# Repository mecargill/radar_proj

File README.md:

You can find a description of this radar project on https://mecargill.github.io/portfolio_page/.

Mcu_fmcw_manager is code for an STM32 f446. It buffers data from the ADC and sends it over SPI to the master (a raspberry pi in my case).
It also sends a triangle wave to the DAC.

Fmcw_pcb contains the KiCAD project in which I made the schematic and PCB for the radar.

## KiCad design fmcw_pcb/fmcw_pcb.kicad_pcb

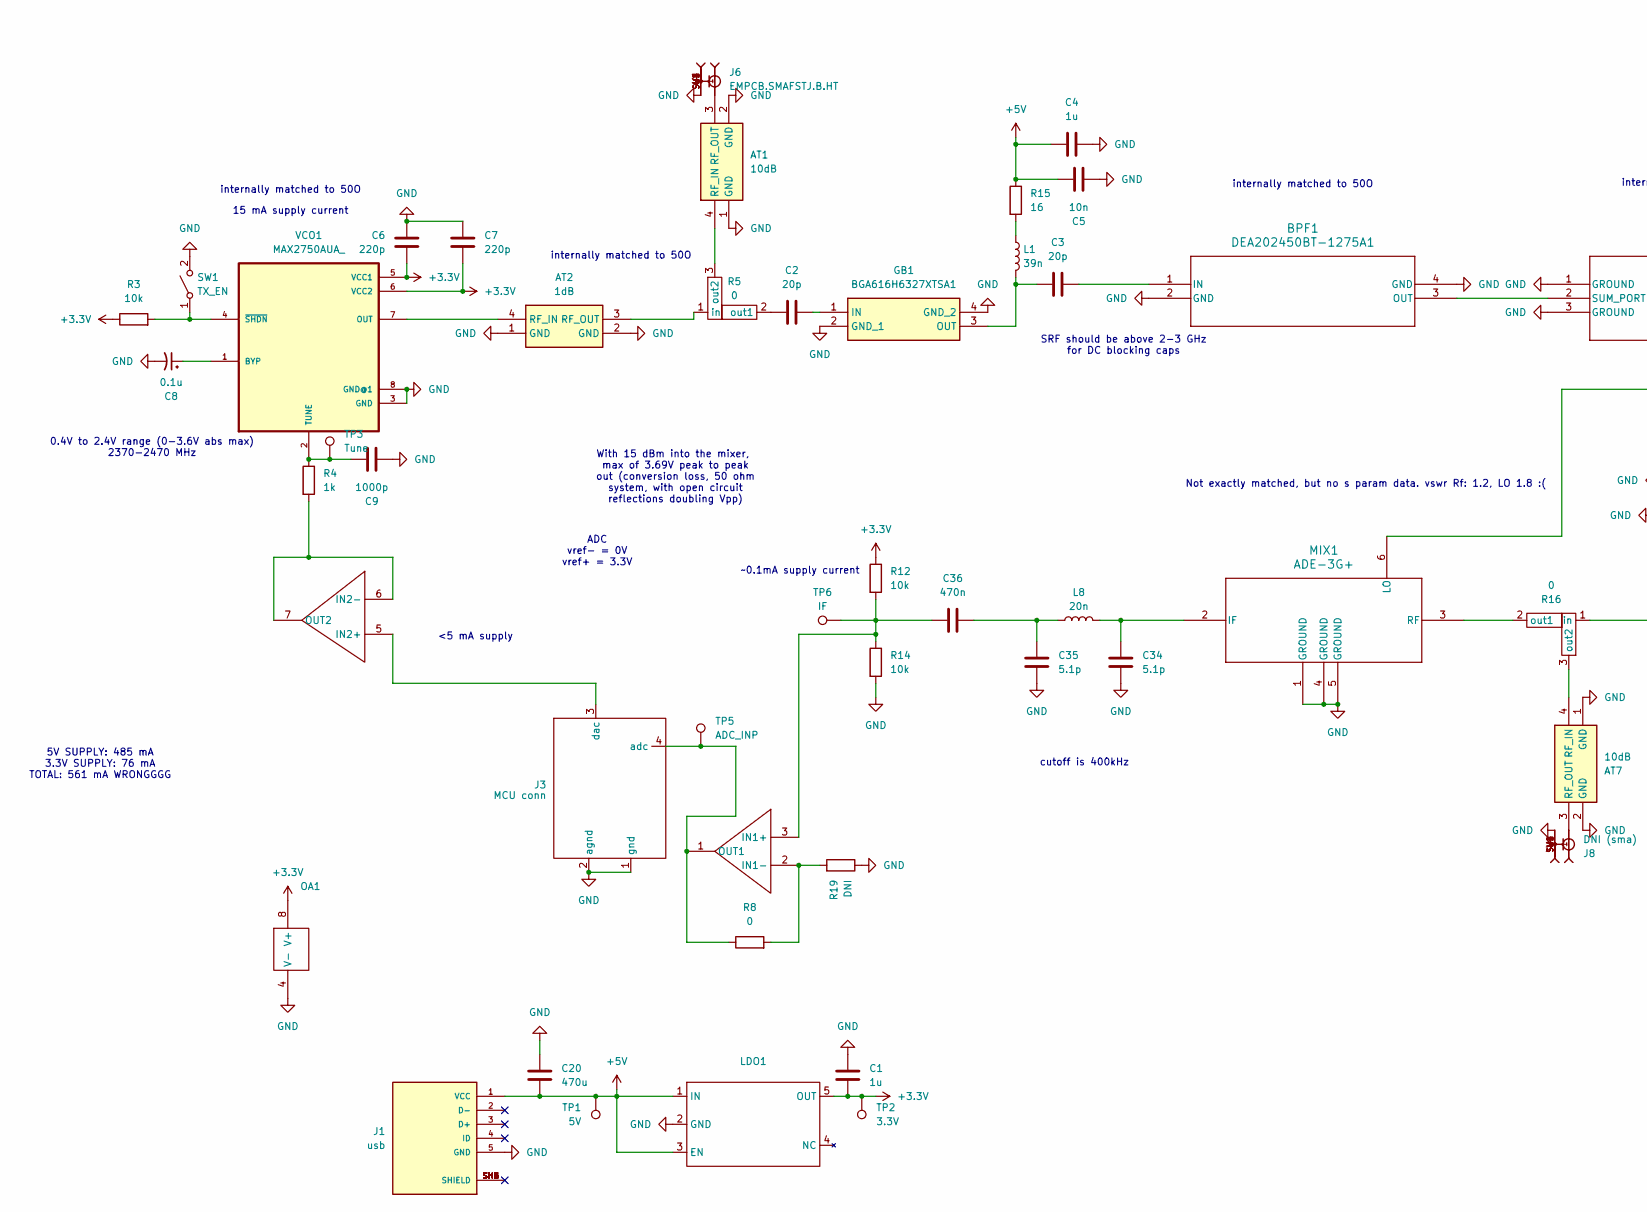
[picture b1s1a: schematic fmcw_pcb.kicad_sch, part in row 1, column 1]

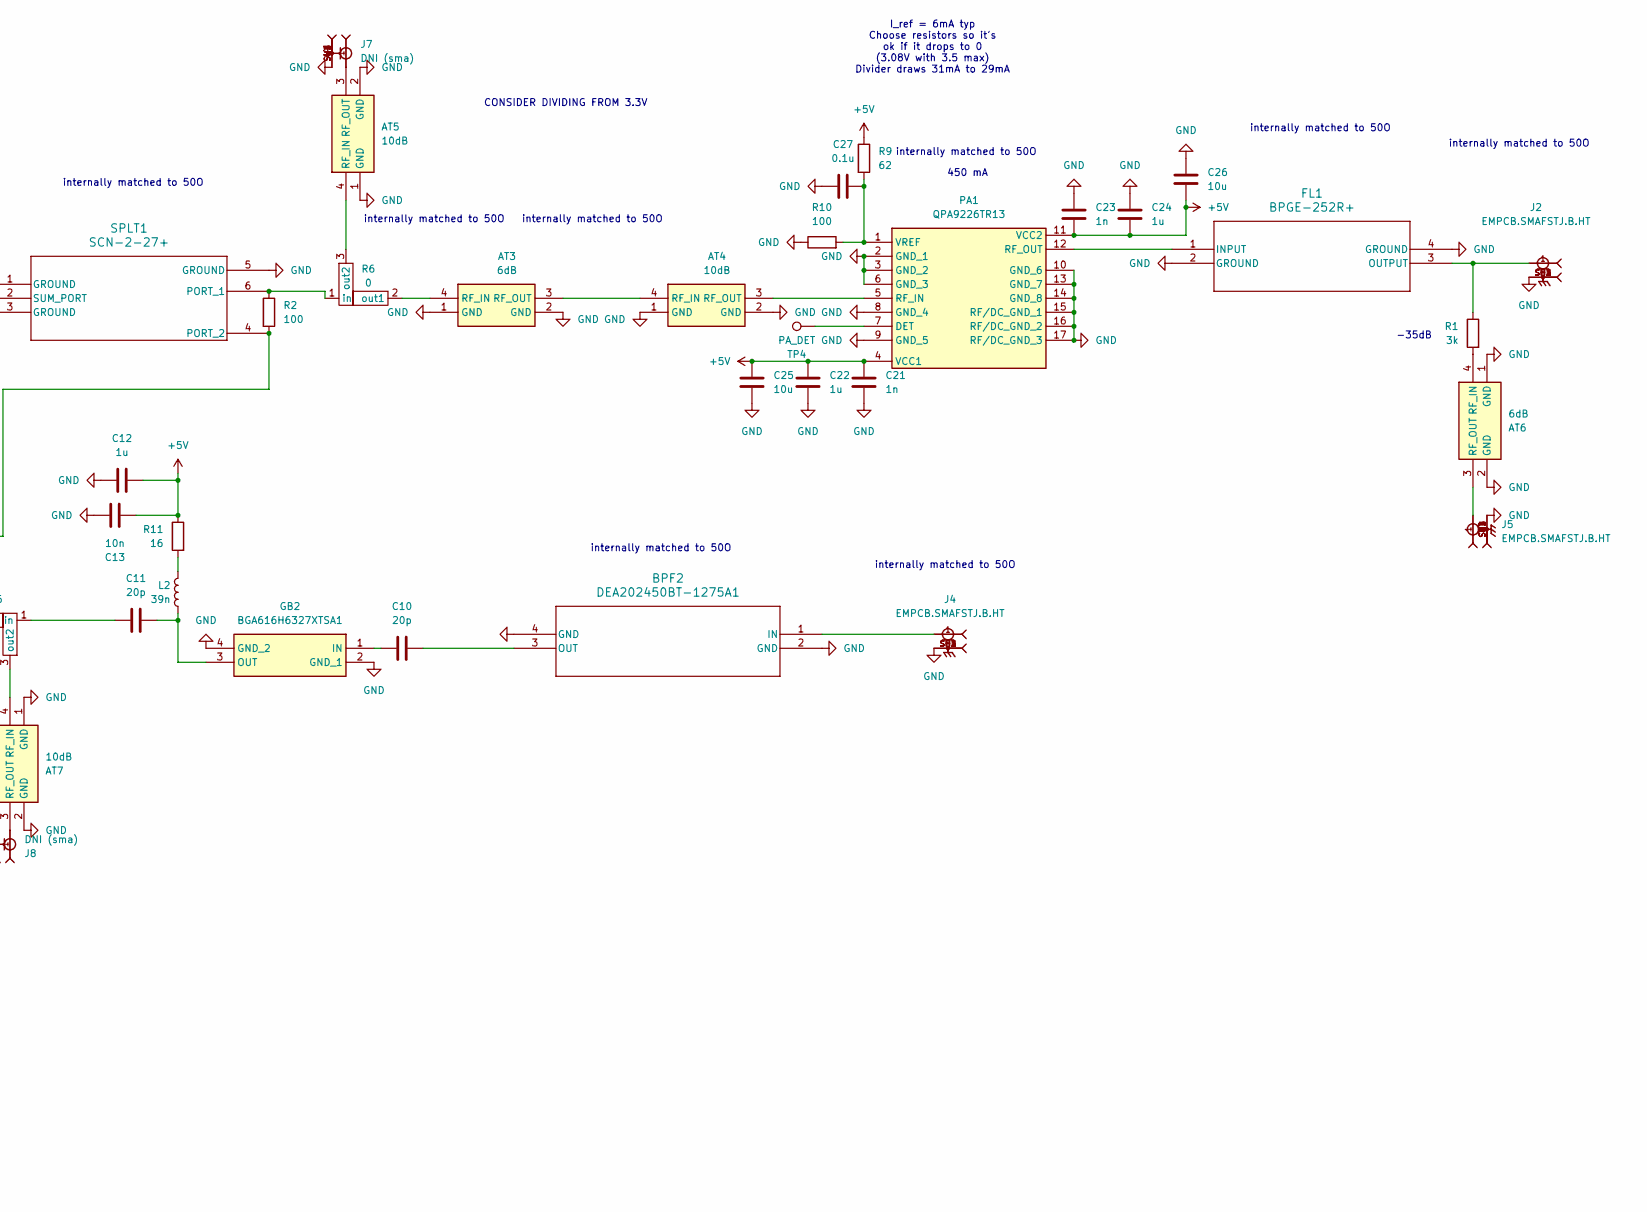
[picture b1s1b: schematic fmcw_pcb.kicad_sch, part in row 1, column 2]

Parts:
AT1, AT4, AT5, AT7: 10dB; EXB24AT6AR5X; Manufacturer_Part_Number EXB-24AT6AR5X; Mouser Part Number 667-EXB-24AT6AR5X
AT2: 1dB; EXB24AT6AR5X; Manufacturer_Part_Number EXB-24AT6AR5X; Mouser Part Number 667-EXB-24AT6AR5X
AT3, AT6: 6dB; EXB24AT6AR5X; Manufacturer_Part_Number EXB-24AT6AR5X; Mouser Part Number 667-EXB-24AT6AR5X
BPF1, BPF2: DEA202450BT-1275A1; DEA-4_2P0X1P25
C1, C4, C12, C22, C24: 1u; C_0805_2012Metric
C2, C3, C10, C11: 20p; C_0603_1608Metric
C5, C13: 10n; C_0805_2012Metric
C6, C7: 220p; C_0603_1608Metric
C8, C27: 0.1u; C_0805_2012Metric
C9: 1000p; C_0805_2012Metric
C20: 470u; CP_Radial_D7.5mm_P2.50mm
C21, C23: 1n; C_0805_2012Metric
C25, C26: 10u; CP_EIA-6032-15_Kemet-U
C34, C35: 5.1p; C_0603_1608Metric
C36: 470n; C_0805_2012Metric
FL1: BPGE-252R+; GE0805C-3_MNC
GB1, GB2: BGA616H6327XTSA1; Manufacturer_Part_Number BGA616H6327XTSA1; Mouser Part Number 726-BGA616H6327XTSA1
J1: usb; AMPHENOL_10118194-0001LF; PARTREV D
J2, J4, J5, J6: EMPCB.SMAFSTJ.B.HT; sma_1.6mm; DigiKey_Part_Number 931-1175-ND
J3: MCU conn; FanPinHeader_1x04_P2.54mm_Vertical
J7, J8: DNI (sma); sma_1.6mm; DigiKey_Part_Number 931-1175-ND
L1, L2: 39n; L_0603_1608Metric
L8: 20n; L_0603_1608Metric
LDO1: SOT95P280X145-5N(ldo)
MIX1: ADE-3G+; Mini-Circuits_CD542_LandPatternPL-052
OA1: SOT65P280X110-8N(op_amp)
PA1: QPA9226TR13; Mouser Part Number 772-QPA9226TR13
R1: 3k; R_0805_2012Metric
R2, R10: 100; R_0805_2012Metric
R3, R12, R14: 10k; R_0805_2012Metric
R4: 1k; R_0805_2012Metric
R5, R6, R16: 0; 2way_jumper
R8: 0; R_0805_2012Metric
R9: 62; R_0805_2012Metric
R11, R15: 16; R_0805_2012Metric
R19: DNI; R_0805_2012Metric
SPLT1: SCN-2-27+; Filter_Mini-Circuits_FV1206-1
SW1: TX_EN; PinHeader_1x02_P2.54mm_Vertical
TP1: 5V; TestPoint_Pad_2.5x2.5mm
TP2: 3.3V; TestPoint_Pad_2.5x2.5mm
TP3: Tune; TestPoint_Pad_2.5x2.5mm
TP4: PA_DET; TestPoint_Pad_2.5x2.5mm
TP5: ADC_INP; TestPoint_Pad_2.5x2.5mm
TP6: IF; TestPoint_Pad_2.5x2.5mm
VCO1: MAX2750AUA_; SOP65P490X110-8N; DigiKey_Part_Number MAX2750AUA+-ND

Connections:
+3.3V: C1.2, C6.2, C7.2, LDO1.5 (OUT), OA1.8 (V+), R3.1, R12.1, TP2.1, VCO1.5 (VCC1), VCO1.6 (VCC2); also elsewhere on the board
+5V: C4.1, C5.1, C12.1, C13.1, C20.1, C21.1, C22.1, C23.2, C24.2, C25.1, C26.2, J1.1 (VCC), LDO1.1 (IN), LDO1.3 (EN), PA1.4 (VCC1), PA1.11 (VCC2), R9.1, R11.1, R15.1, TP1.1; also elsewhere on the board
GND: AT1.1 (GND), AT1.2 (GND), AT2.1 (GND), AT2.2 (GND), AT3.1 (GND), AT3.2 (GND), AT4.1 (GND), AT4.2 (GND), AT5.1 (GND), AT5.2 (GND), AT6.1 (GND), AT6.2 (GND), AT7.1 (GND), AT7.2 (GND), BPF1.2 (GND), BPF1.4 (GND), BPF2.2 (GND), BPF2.4 (GND), C1.1, C4.2, C5.2, C6.1, C7.1, C8.2, C9.2, C12.2, C13.2, C20.2, C21.2, C22.2, C23.1, C24.1, C25.2, C26.1, C27.1, C34.1, C35.1, FL1.2 (GROUND), FL1.4 (GROUND), GB1.2 (GND_1), GB1.4 (GND_2), GB2.2 (GND_1), GB2.4 (GND_2), J1.5 (GND), J2.SH1, J2.SH2, J2.SH3, J2.SH4, J3.1 (gnd), J3.2 (agnd), J4.SH1, J4.SH2, J4.SH3, J4.SH4, J5.SH1, J5.SH2, J5.SH3, J5.SH4, J6.SH1, J6.SH2, J6.SH3, J6.SH4, J7.SH1, J7.SH2, J7.SH3, J7.SH4, J8.SH1, J8.SH2, J8.SH3, J8.SH4, LDO1.2 (GND), MIX1.1 (GROUND), MIX1.4 (GROUND), MIX1.5 (GROUND), OA1.4 (V-), PA1.2 (GND_1), PA1.3 (GND_2), PA1.6 (GND_3), PA1.8 (GND_4), PA1.9 (GND_5), PA1.10 (GND_6), PA1.13 (GND_7), PA1.14 (GND_8), PA1.15 (RF/DC_GND_1), PA1.16 (RF/DC_GND_2), PA1.17 (RF/DC_GND_3), R10.1, R14.2, R19.1, SPLT1.1 (GROUND), SPLT1.3 (GROUND), SPLT1.5 (GROUND), SW1.2 (B), VCO1.3 (GND), VCO1.8 (GND@1)
unnamed: AT1.4 (RF_IN), R5.3 (out2)
unnamed: AT1.3 (RF_OUT), J6.1
unnamed: AT2.4 (RF_IN), VCO1.7 (OUT)
unnamed: AT2.3 (RF_OUT), R5.1 (in)
unnamed: AT3.4 (RF_IN), R6.2 (out1)
unnamed: AT3.3 (RF_OUT), AT4.4 (RF_IN)
unnamed: AT4.3 (RF_OUT), PA1.5 (RF_IN)
unnamed: AT5.4 (RF_IN), R6.3 (out2)
unnamed: AT5.3 (RF_OUT), J7.1
unnamed: AT6.4 (RF_IN), R1.2
unnamed: AT6.3 (RF_OUT), J5.1
unnamed: AT7.4 (RF_IN), R16.3 (out2)
unnamed: AT7.3 (RF_OUT), J8.1
unnamed: BPF1.1 (IN), C3.2
unnamed: BPF1.3 (OUT), SPLT1.2 (SUM_PORT)
unnamed: BPF2.1 (IN), J4.1
unnamed: BPF2.3 (OUT), C10.1
unnamed: C35.2, C36.2, L8.1
unnamed: FL1.1 (INPUT), PA1.12 (RF_OUT)
unnamed: FL1.3 (OUTPUT), J2.1, R1.1
unnamed: C2.2, GB1.1 (IN)
unnamed: C3.1, GB1.3 (OUT), L1.2
unnamed: C10.2, GB2.1 (IN)
unnamed: C11.1, GB2.3 (OUT), L2.2
unnamed 27: J3.4 (adc), OA1.1 (OUT1), R8.1, TP5.1; also elsewhere on the board
unnamed: J3.3 (dac), OA1.5 (IN2+)
unnamed: L1.1, R15.2
unnamed: L2.1, R11.2
unnamed: C34.2, L8.2, MIX1.2 (IF)
unnamed: MIX1.6 (LO), R2.2, SPLT1.4 (PORT_2)
unnamed: MIX1.3 (RF), R16.2 (out1)
unnamed 34: C36.1, OA1.3 (IN1+), R12.2, R14.1, TP6.1; also elsewhere on the board
unnamed: OA1.2 (IN1-), R8.2, R19.2
unnamed: OA1.6 (IN2-), OA1.7 (OUT2), R4.2
unnamed 37: PA1.7 (DET), TP4.1; also elsewhere on the board
unnamed: C27.2, PA1.1 (VREF), R9.2, R10.2
unnamed: C2.1, R5.2 (out1)
unnamed: R2.1, R6.1 (in), SPLT1.6 (PORT_1)
unnamed: C11.2, R16.1 (in)
unnamed: R3.2, SW1.1 (A), VCO1.4 (~SHDN)
unnamed: C8.1, VCO1.1 (BYP)
unnamed 44: C9.1, R4.1, TP3.1, VCO1.2 (TUNE); also elsewhere on the board

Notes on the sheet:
internally matched to 50O
Not exactly matched, but no s param data. vswr Rf: 1.2, LO 1.8 :(
I_ref = 6mA typ Choose resistors so it's ok if it drops to 0 (3.08V with 3.5 max) Divider draws 31mA to 29mA
With 15 dBm into the mixer, max of 3.69V peak to peak out (conversion loss, 50 ohm system, with open circuit reflections doubling Vpp)
<5 mA supply
cutoff is 400kHz
0.4V to 2.4V range (0-3.6V abs max) 2370-2470 MHz
450 mA
ADC vref- = 0V vref+ = 3.3V
~0.1mA supply current
CONSIDER DIVIDING FROM 3.3V
15 mA supply current
-35dB
SRF should be above 2-3 GHz for DC blocking caps
5V SUPPLY: 485 mA 3.3V SUPPLY: 76 mA TOTAL: 561 mA WRONGGGG

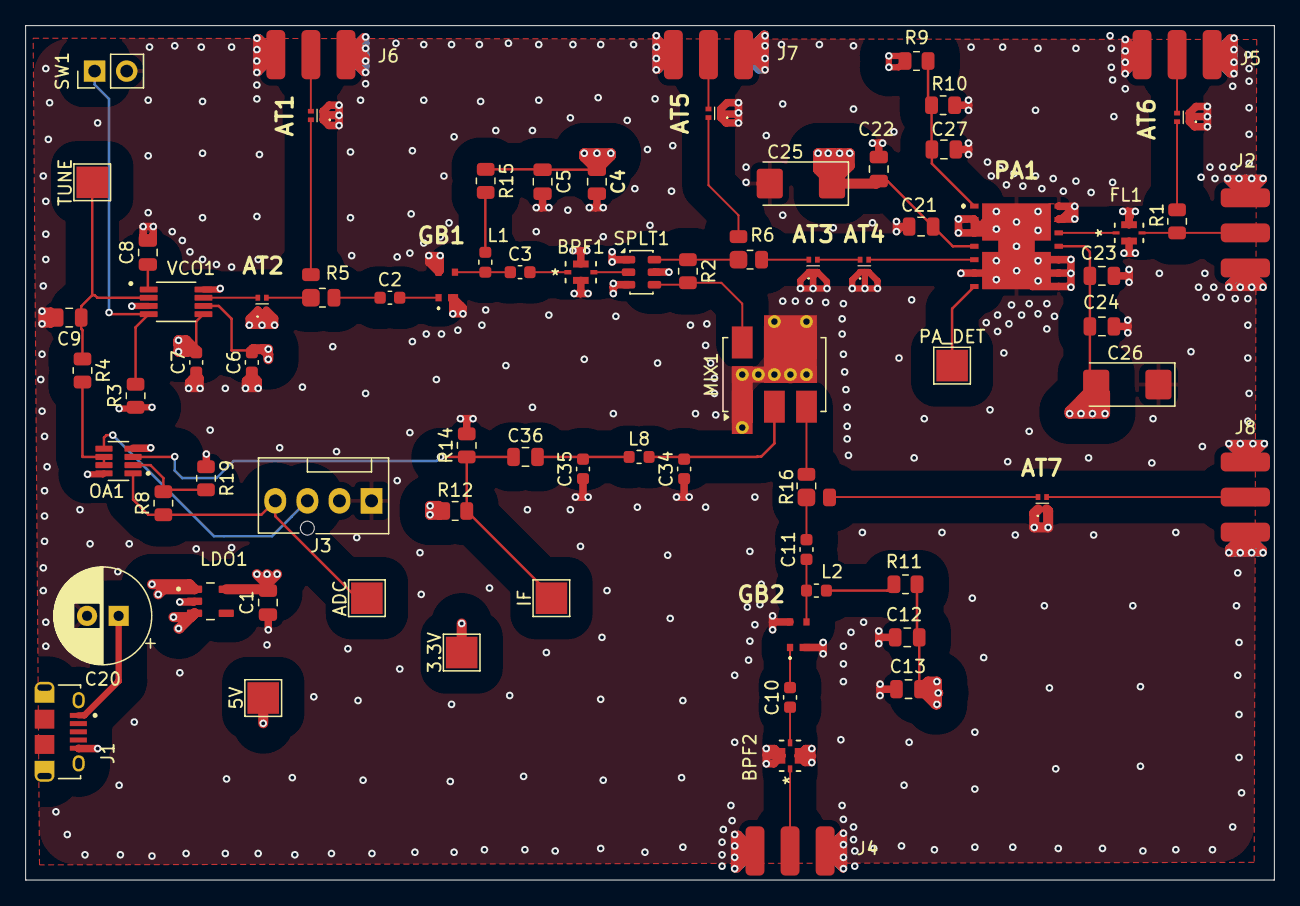
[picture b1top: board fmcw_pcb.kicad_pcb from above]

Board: 4 copper layers, 98.8 x 67.6 mm, 75 parts (0 on the bottom side), 45 nets.

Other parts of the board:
3.3V: 3.3V; TestPoint_Pad_2.5x2.5mm
5V: 5V; TestPoint_Pad_2.5x2.5mm
ADC: ADC_INP; TestPoint_Pad_2.5x2.5mm
IF: IF; TestPoint_Pad_2.5x2.5mm
PA_DET: PA_DET; TestPoint_Pad_2.5x2.5mm
TUNE: Tune; TestPoint_Pad_2.5x2.5mm

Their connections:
+3.3V: 3.3V.1; also elsewhere on the board
+5V: 5V.1; also elsewhere on the board
unnamed 27: ADC.1; also elsewhere on the board
unnamed 34: IF.1; also elsewhere on the board
unnamed 37: PA_DET.1; also elsewhere on the board
unnamed 44: TUNE.1; also elsewhere on the board

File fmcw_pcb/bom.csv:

"Reference","Value","Datasheet","Footprint","Qty","DNP"
"AT1,AT4,AT5,AT7","10dB","http://industrial.panasonic.com/www-cgi/jvcr13pz.cgi?E+PZ+3+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","my_footprints:EXB24AT6AR5X","4",""
"AT2","1dB","http://industrial.panasonic.com/www-cgi/jvcr13pz.cgi?E+PZ+3+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","my_footprints:EXB24AT6AR5X","1",""
"AT3,AT6","6dB","http://industrial.panasonic.com/www-cgi/jvcr13pz.cgi?E+PZ+3+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","my_footprints:EXB24AT6AR5X","2",""
"BPF1,BPF2","DEA202450BT-1275A1","DEA202450BT-1275A1","my_footprints:DEA-4_2P0X1P25","2",""
"C1,C4,C12,C22,C24","1u","~","Capacitor_SMD:C_0805_2012Metric","5",""
"C2,C3,C10,C11","20p","~","Capacitor_SMD:C_0603_1608Metric","4",""
"C5,C13","10n","~","Capacitor_SMD:C_0805_2012Metric","2",""
"C6,C7","220p","~","Capacitor_SMD:C_0603_1608Metric","2",""
"C8,C27","0.1u","~","Capacitor_SMD:C_0805_2012Metric","2",""
"C9","1000p","~","Capacitor_SMD:C_0805_2012Metric","1",""
"C20","470u","~","Capacitor_THT:CP_Radial_D7.5mm_P2.50mm","1",""
"C21,C23","1n","~","Capacitor_SMD:C_0805_2012Metric","2",""
"C25,C26","10u","~","Capacitor_Tantalum_SMD:CP_EIA-6032-15_Kemet-U","2",""
"C34,C35","5.1p","~","Capacitor_SMD:C_0603_1608Metric","2",""
"C36","470n","~","Capacitor_SMD:C_0805_2012Metric","1",""
"FL1","BPGE-252R+","BPGE-252R+","my_footprints:GE0805C-3_MNC","1",""
"GB1,GB2","BGA616H6327XTSA1","https://www.infineon.com/dgdl/Infineon-BGA616-DS-v02_01-en.p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","my_footprints:BGA616H6327XTSA1","2",""
"J1","usb","","my_footprints:AMPHENOL_10118194-0001LF","1",""
"J2,J4,J5,J6","EMPCB.SMAFSTJ.B.HT","","my_footprints:sma_1.6mm","4",""
"J3","MCU conn","","Connector:FanPinHeader_1x04_P2.54mm_Vertical","1",""
"J7,J8","DNI (sma)","","my_footprints:sma_1.6mm","2",""
"L1,L2","39n","~","Inductor_SMD:L_0603_1608Metric","2",""
"L8","20n","~","Inductor_SMD:L_0603_1608Metric","1",""
"LDO1,OA1","~","","-- mixed values --","2",""
"MIX1","ADE-3G+","ADE-3G+","RF_Mini-Circuits:Mini-Circuits_CD542_LandPatternPL-052","1",""
"PA1","QPA9226TR13","https://www.qorvo.com/products/d/da005895","my_footprints:QPA9226TR13","1",""
"R1","3k","~","Resistor_SMD:R_0805_2012Metric","1",""
"R2,R10","100","~","Resistor_SMD:R_0805_2012Metric","2",""
"R3,R12,R14","10k","~","Resistor_SMD:R_0805_2012Metric","3",""
"R4","1k","~","Resistor_SMD:R_0805_2012Metric","1",""
"R5,R6,R8,R16","0","-- mixed values --","-- mixed values --","4",""
"R9","62","~","Resistor_SMD:R_0805_2012Metric","1",""
"R11,R15","16","~","Resistor_SMD:R_0805_2012Metric","2",""
"R19","DNI","~","Resistor_SMD:R_0805_2012Metric","1",""
"SPLT1","SCN-2-27+","SCN-2-27+","Filter:Filter_Mini-Circuits_FV1206-1","1",""
"SW1","TX_EN","~","Connector_PinHeader_2.54mm:PinHeader_1x02_P2.54mm_Vertical","1",""
"TP1","5V","~","TestPoint:TestPoint_Pad_2.5x2.5mm","1",""
"TP2","3.3V","~","TestPoint:TestPoint_Pad_2.5x2.5mm","1",""
"TP3","Tune","~","TestPoint:TestPoint_Pad_2.5x2.5mm","1",""
"TP4","PA_DET","~","TestPoint:TestPoint_Pad_2.5x2.5mm","1",""
"TP5","ADC_INP","~","TestPoint:TestPoint_Pad_2.5x2.5mm","1",""
"TP6","IF","~","TestPoint:TestPoint_Pad_2.5x2.5mm","1",""
"VCO1","MAX2750AUA_","","my_footprints:SOP65P490X110-8N","1",""

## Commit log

2025-07-07 Add folders
2025-07-14 Add rest of design files
2025-07-16 Added find chirps algorithm, doppler works now
